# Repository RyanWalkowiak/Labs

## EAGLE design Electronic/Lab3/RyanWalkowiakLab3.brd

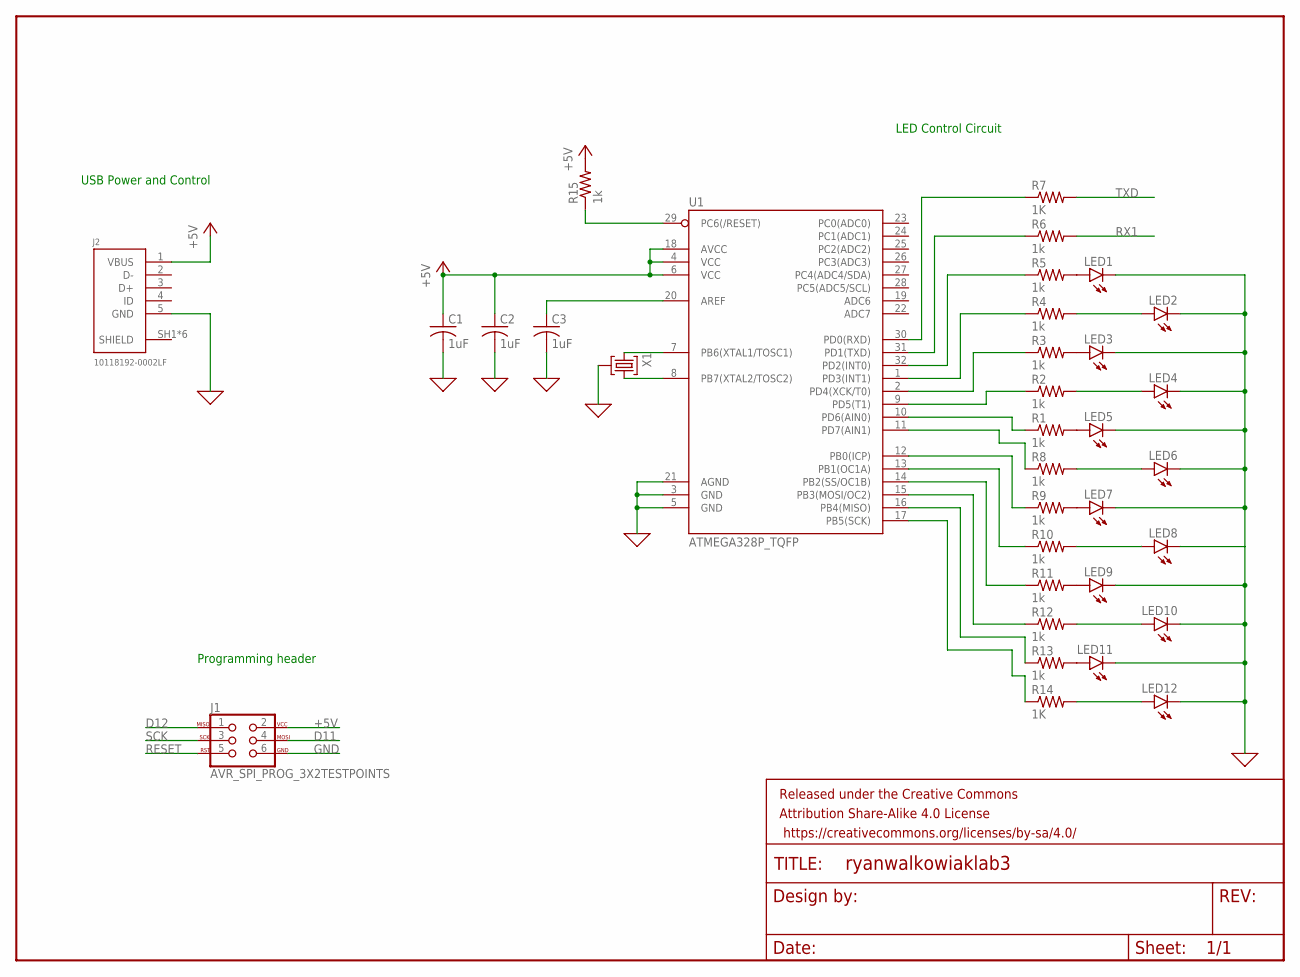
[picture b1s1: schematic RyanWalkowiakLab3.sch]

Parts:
C1, C2, C3: 1uF; C0805
FRAME1: FRAME-LETTERNO_PACKAGE; DUMMY
J1: AVR_SPI_PROG_3X2TESTPOINTS; 2X3_TEST_POINTS
J2: 10118192-0002LF
LED1, LED2, LED3, LED4, LED5, LED6, LED7, LED8, LED9, LED10, LED11, LED12: LEDCHIP-LED0805; CHIP-LED0805
R1, R2, R3, R4, R5, R6, R8, R9, R10, R11, R12, R13, R15: 1k; R0805
R7, R14: 1K; R0805
U1: ATMEGA328P_TQFP; TQFP32-08
X1: 16Mhz; CSTCE16M0V53-R0

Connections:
0: C1.2, C2.2, C3.2, J2.5 (GND), J2.SH1 (SHIELD), J2.SH2 (SHIELD), J2.SH3 (SHIELD), J2.SH4 (SHIELD), J2.SH5 (SHIELD), J2.SH6 (SHIELD), LED1.C, LED2.C, LED3.C, LED4.C, LED5.C, LED6.C, LED7.C, LED8.C, LED9.C, LED10.C, LED11.C, LED12.C, U1.3 (GND), U1.5 (GND), U1.21 (AGND), X1.2 (GND)
+5V: C1.1, C2.1, J1.2, J2.1 (VBUS), R15.2, U1.4 (VCC), U1.6 (VCC), U1.18 (AVCC)
D11: J1.4
D12: J1.1
GND: J1.6
unnamed: R7.1, U1.30 (PD0(RXD))
unnamed: R6.1, U1.31 (PD1(TXD))
unnamed: R5.1, U1.32 (PD2(INT0))
unnamed: R4.1, U1.1 (PD3(INT1))
unnamed: R3.1, U1.2 (PD4(XCK/T0))
unnamed: R2.1, U1.9 (PD5(T1))
unnamed: R1.1, U1.10 (PD6(AIN0))
unnamed: R8.1, U1.11 (PD7(AIN1))
unnamed: R9.1, U1.12 (PB0(ICP))
unnamed: R10.1, U1.13 (PB1(OC1A))
unnamed: R11.1, U1.14 (PB2(SS/OC1B))
unnamed: R12.1, U1.15 (PB3(MOSI/OC2))
unnamed: R13.1, U1.16 (PB4(MISO))
unnamed: R14.1, U1.17 (PB5(SCK))
unnamed: LED1.A, R5.2
unnamed: LED3.A, R3.2
unnamed: LED5.A, R1.2
unnamed: LED7.A, R9.2
unnamed: LED9.A, R11.2
unnamed: LED11.A, R13.2
unnamed: LED2.A, R4.2
unnamed: R15.1, U1.29 (PC6(/RESET))
unnamed: C3.1, U1.20 (AREF)
unnamed: LED4.A, R2.2
unnamed: LED6.A, R8.2
unnamed: LED8.A, R10.2
unnamed: LED10.A, R12.2
unnamed: LED12.A, R14.2
unnamed: U1.7 (PB6(XTAL1/TOSC1)), X1.1 (INPUT)
unnamed: U1.8 (PB7(XTAL2/TOSC2)), X1.3 (OUTPUT)
RESET: J1.5
RX1: R6.2
SCK: J1.3
TXD: R7.2

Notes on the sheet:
Programming header
USB Power and Control
LED Control Circuit

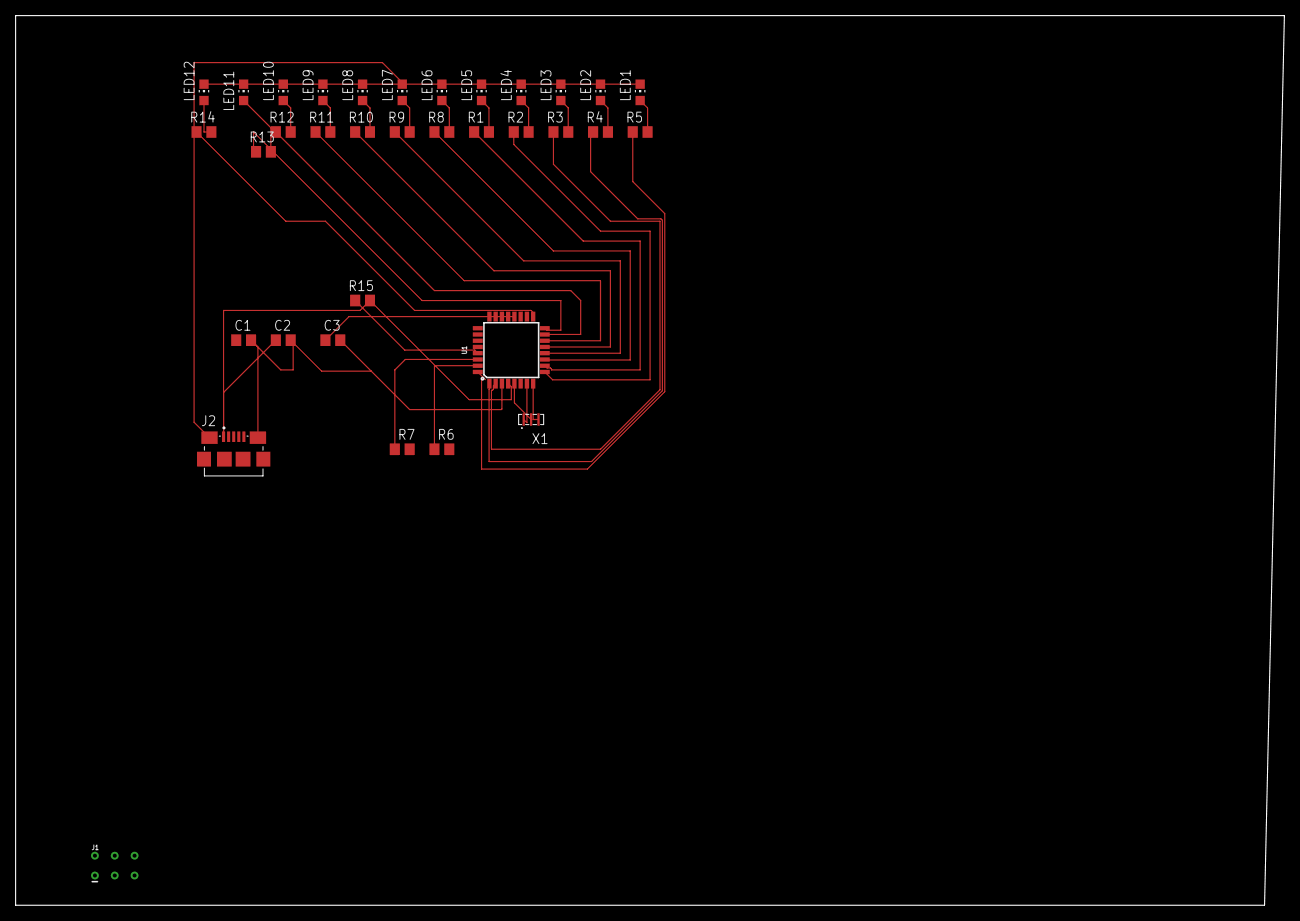
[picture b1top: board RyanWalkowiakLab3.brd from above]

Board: 2 copper layers, 162.5 x 114.0 mm, 35 parts (0 on the bottom side), 32 nets.

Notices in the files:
parts and their libraries:
SparkFun-Aesthetics: Licensing: Creative Commons ShareAlike 4.0 International - https://creativecommons.org/licenses/by-sa/4.0
SparkFun-Aesthetics: Released under the Creative Commons Attribution Share-Alike 4.0 License
SparkFun-Aesthetics: https://creativecommons.org/licenses/by-sa/4.0
